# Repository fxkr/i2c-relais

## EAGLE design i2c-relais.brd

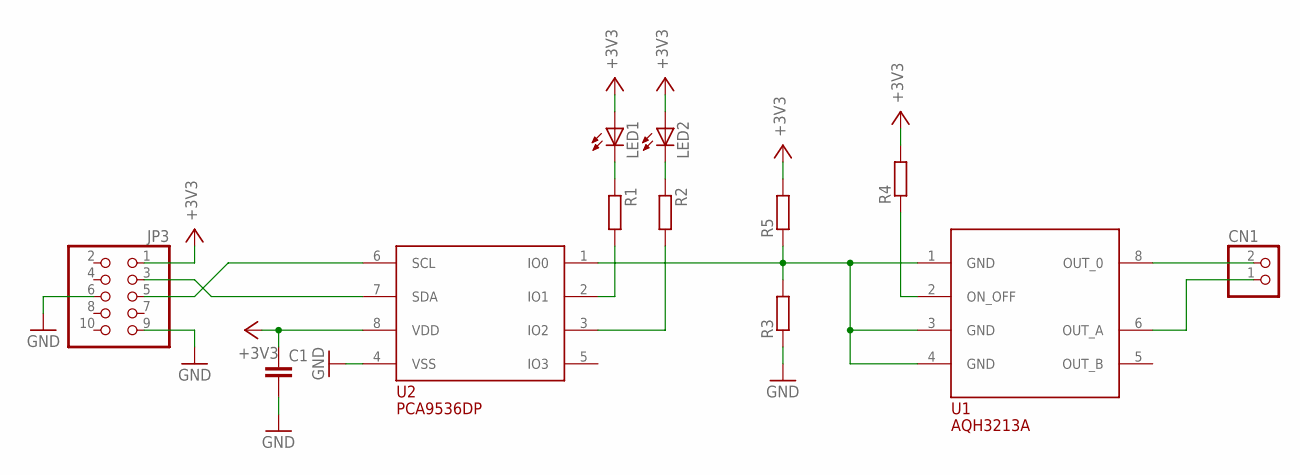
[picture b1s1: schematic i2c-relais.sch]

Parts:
C1: C-EUC0805; C0805
CN1: JST_2PIN-SMT-RA; JST-PH-2-SMT-RA
JP3: PINHD-2X5; 2X05
LED1, LED2: LEDCHIPLED_0805; CHIPLED_0805
R1, R2, R3, R4, R5: R-EU_M0805; M0805
U1: AQH3213A; DIP8
U2: PCA9536DP; TSSOP8

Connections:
GND: C1.2, JP3.6, JP3.9, R3.1, U2.4 (VSS)
unnamed: R3.2, R5.1, U1.1 (GND), U1.3 (GND), U1.4 (GND), U2.1 (IO0)
unnamed: CN1.1 (2), U1.6 (OUT_A)
unnamed: CN1.2 (1), U1.8 (OUT_0)
unnamed: R4.1, U1.2 (ON_OFF)
unnamed: R2.2, U2.3 (IO2)
unnamed: LED1.C, R1.1
unnamed: LED2.C, R2.1
R1: R1.2, U2.2 (IO1)
SCL: JP3.5, U2.6 (SCL)
SDA: JP3.3, U2.7 (SDA)
U2: C1.1, JP3.1, LED1.A, LED2.A, R4.2, R5.2, U2.8 (VDD)

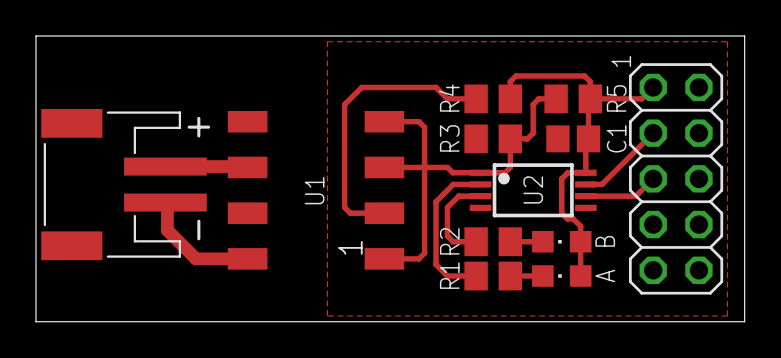
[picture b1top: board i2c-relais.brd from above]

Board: 2 copper layers, 39.4 x 15.9 mm, 12 parts (0 on the bottom side), 12 nets.

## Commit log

2015-10-20 Add .gitignore
2015-10-20 Import r0 sch + brd + lbrs
